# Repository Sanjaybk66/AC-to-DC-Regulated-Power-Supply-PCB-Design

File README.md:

# AC to DC Voltage Regulator PCB Design

This project presents the design of an AC to DC regulated power supply PCB using KiCad. The circuit uses a full-wave bridge rectifier, filtering capacitors, and a voltage regulator to provide a stable DC output suitable for embedded systems and low-power electronics. It serves as a practical and learning-oriented reference for understanding power supply design and PCB layout in KiCad.

## Features
- Full-wave bridge rectifier using 1N4007 diodes
- Smoothing capacitor for ripple reduction
- Power ON LED indicator
- Linear voltage regulator (AMS1117)
- Stable DC output suitable for microcontrollers
- Designed using KiCad with beginner-friendly schematic and PCB layout  

## Power Flow
AC Input → Bridge Rectifier → Filter Capacitor → Voltage Regulator → DC Output

## Applications
- Embedded systems
- ESP32 projects
- Electronics laboratory experiments

## Tools
- KiCad (schematic and PCB layout)
  
## Schematic
[Schematic pdf](https://github.com/Sanjaybk66/AC-to-DC-Regulated-Power-Supply-PCB-Design/blob/main/VOLTAGE%20REGULATOR_Schematic_Pdf)

##PCB Layout

## PCB 3D View

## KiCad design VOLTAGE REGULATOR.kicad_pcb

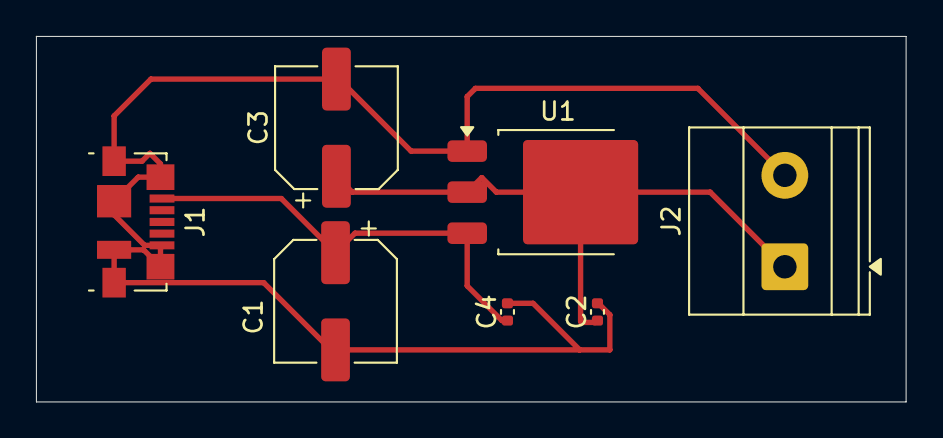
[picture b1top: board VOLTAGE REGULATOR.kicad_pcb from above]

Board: 2 copper layers, 48.3 x 20.3 mm, 7 parts (0 on the bottom side), 3 nets.

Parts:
C1, C3: 22u; CP_Elec_6.3x7.7
C2, C4: 100n; C_0402_1005Metric
J1: USB_B_Micro; USB_Micro-B_Molex_47346-0001
J2: Screw_Terminal_01x02; TerminalBlock_Phoenix_MKDS-1,5-2-5.08_1x02_P5.08mm_Horizont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
U1: AMS1117CD-3.3; TO-252-3_TabPin2

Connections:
+3.3V: C2.1, C3.1, J2.1, U1.2 (VO)
+5V: C1.1, C4.1, J1.1 (VBUS), U1.3 (VI)
GND: C1.2, C2.2, C3.2, C4.2, J1.5 (GND), J1.6 (Shield), J2.2, U1.1 (GND)

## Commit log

2026-02-08 Enhance README with detailed project overview and features
    Expanded project description and added features, applications, and tools sections for clarity.
2026-02-08 Add schematic image to README
2026-02-08 VOLTAGE REGULATOR_Schematic_Pdf
